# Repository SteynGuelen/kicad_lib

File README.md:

# KiCad libraries

Custom symbols, footprints, 3D models, drawing sheets, and reusable design blocks by Steyn Guelen.

## Requirements

Use KiCad 10 or newer for the complete collection. Some files were saved with KiCad 10; older versions may not open all assets. Git is optional if you download a ZIP instead.

## Install

1. Clone this repository into a permanent location:

   ```sh
   git clone https://github.com/SteynGuelen/kicad_lib.git
   ```

   Alternatively, choose **Code → Download ZIP** on GitHub and extract it.

2. Open **Preferences → Manage Symbol Libraries**. Select **Global Libraries** to make the symbols available to all projects, or **Project Specific Libraries** for the current project. Click **Add existing library** and select the `.kicad_sym` files inside `symbols/`.

3. Open **Preferences → Manage Footprint Libraries**. Add the `.pretty` directories inside `footprints/` as existing libraries. Select directories, rather than the individual `.kicad_mod` files. Keep the directory names as library nicknames, for example `integrated_circuits` and `standards`.

## Install the MPlab project template

The `templates/MPlab/` folder contains the MPlab project template, including its schematics, PCB, embedded drawing sheets, and template preview.

1. In KiCad, open **Preferences → Configure Paths** and find `KICAD_USER_TEMPLATE_DIR`. This is your user template folder.
2. Copy the entire `templates/MPlab/` folder into that folder. The resulting layout should be `<user template folder>/MPlab/meta/info.html`, with the project files directly inside `MPlab/`.

   For example, on this Mac the destination is:

   ```text
   /Users/steyn/Documents/KiCad/10.0/template/MPlab/
   ```

   If a copy already exists, back it up before replacing it.

3. In KiCad’s Project Manager, choose **File → New Project from Template**, open **User Templates**, and select **MPLab**. Choose a new project name and location to create your own project from the template.

See [KiCad’s template documentation](https://docs.kicad.org/10.0/en/kicad/kicad.pdf) for details about user template locations.

## Other assets

- `design_blocks/`: reusable KiCad design-block libraries. Add the `.kicad_blocks` directory through KiCad’s design-block library manager.

## Update

If installed using Git, run this inside the cloned folder:

```sh
git pull --ff-only
```

For a ZIP installation, download and extract the latest version into the same location. Keep any personal edits backed up before replacing files.

See the [official KiCad documentation](https://docs.kicad.org/) for library management and path configuration.

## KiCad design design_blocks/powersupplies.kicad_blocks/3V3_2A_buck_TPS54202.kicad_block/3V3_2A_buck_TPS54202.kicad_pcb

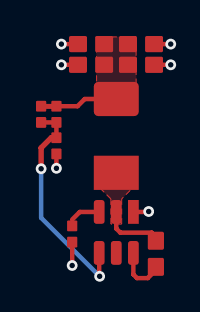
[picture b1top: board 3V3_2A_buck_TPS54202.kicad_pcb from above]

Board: 4 copper layers, 11 parts (0 on the bottom side), 6 nets.

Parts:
C19: 1uF; Capacitor_0603
C20: 100nF; Capacitor_0402
C21: 47pF; Capacitor_0402
C22, C23, C24, C25: 22uF; Capacitor_0603
L8: 4.7uH; L_Changjiang_FXL0530
R19: 100k; Resistor_0402
R20: 22k; Resistor_0402
U4: TPS54202DDC; SOT-23-6

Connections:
+3V3: C21.2, C22.2, C23.2, C24.2, C25.2, L8.2, R19.1
GND: C19.1, C22.1, C23.1, C24.1, C25.1, R20.2, U4.1 (GND)
unnamed: C20.1, U4.6 (BOOT)
unnamed: C21.1, R19.2, R20.1, U4.4 (FB)
unnamed: C20.2, L8.1, U4.2 (SW)
VBUS: C19.2, U4.3 (VIN)
